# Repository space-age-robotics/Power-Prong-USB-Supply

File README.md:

Power-Prong-USB-Supply
======================

Eagle 6.2 Design files for the Power Prong USB power supply.  It has a selectable 5V or 3v3 volt output (or whatever other MCP1824S voltage regulator that you care to use).  

It has a 250mA polyfuse, with an LED indicator that lights up when the fuse is tripped.

It has connectors for wide breadboards (with 2 power 'lanes' on each side) and narrow (with one power 'lane' per side).

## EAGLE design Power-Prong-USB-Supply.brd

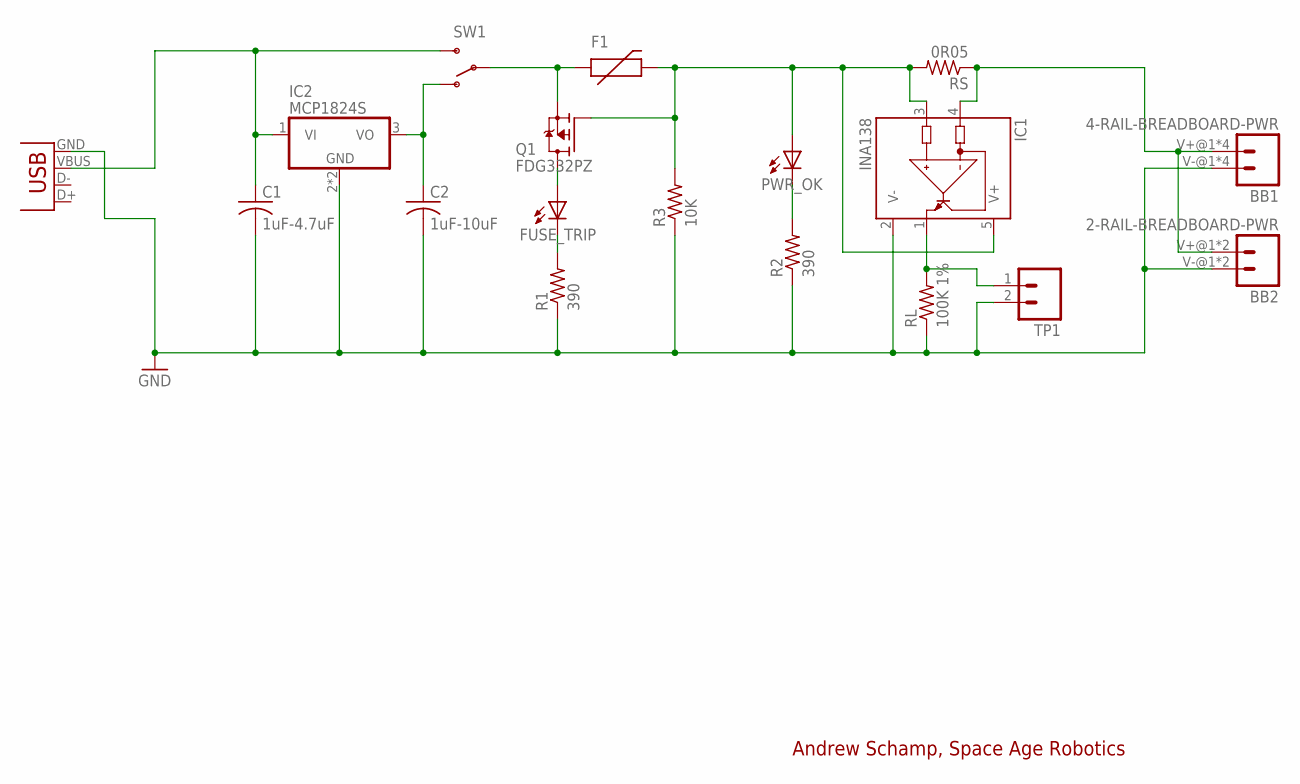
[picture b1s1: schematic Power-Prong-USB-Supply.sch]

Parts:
BB1: 4-RAIL-BREADBOARD-PWR; 4-RAIL-BREADBOARD_X2
BB2: 2-RAIL-BREADBOARD-PWR; 2-RAIL-BREADBOARD
C1: 1uF-4.7uF; C0805
C2: 1uF-10uF; C0805
F1: PTCSMD; PTC-1206
FUSE_TRIP: LEDCHIP-LED0805; CHIP-LED0805
IC1: INA138; SOT23-5
IC2: MCP1824S; SOT223
PWR_OK: LEDCHIP-LED0805; CHIP-LED0805
Q1: FDG332PZ; SC70-6L
R1, R2: 390; R0603
R3: 10K; R0603
RL: 100K 1%; R0805
RS: 0R05; R0805
SW1: SWITCH-SPDTMSH12204; MSH12204
TP1: M023.5MM-NO_SILK; SCREWTERMINAL-3.5MM-2-NS
X1: USBSMD; USB-MINIB

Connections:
GND: BB1.V-@1 (2), BB1.V-@2 (2), BB1.V-@3 (2), BB1.V-@4 (2), BB2.V-@1 (2), BB2.V-@2 (2), C1.2, C2.2, IC1.2 (V-), IC2.2 (GND), IC2.4 (GND), R1.1, R2.1, R3.1, RL.1, TP1.2, X1.GND
unnamed: F1.1, Q1.4 (S), SW1.2
unnamed: C1.1, IC2.1 (VI), SW1.3 (S), X1.VBUS
unnamed: FUSE_TRIP.A, Q1.1 (D), Q1.2 (D), Q1.5 (D), Q1.6 (D)
unnamed: IC1.1 (OUT), RL.2, TP1.1
unnamed: F1.2, IC1.3 (IN+), IC1.5 (V+), PWR_OK.A, Q1.3 (G), R3.2, RS.2
unnamed: PWR_OK.C, R2.2
unnamed: FUSE_TRIP.C, R1.2
unnamed: C2.1, IC2.3 (VO), SW1.1 (O)
VOUT: BB1.V+@1 (1), BB1.V+@2 (1), BB1.V+@3 (1), BB1.V+@4 (1), BB2.V+@1 (1), BB2.V+@2 (1), IC1.4 (IN-), RS.1

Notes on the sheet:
Andrew Schamp, Space Age Robotics

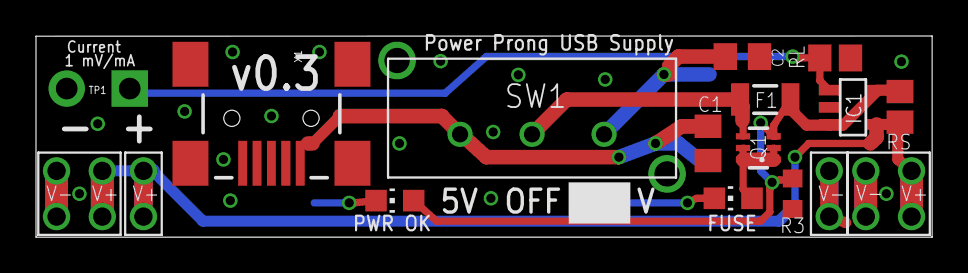
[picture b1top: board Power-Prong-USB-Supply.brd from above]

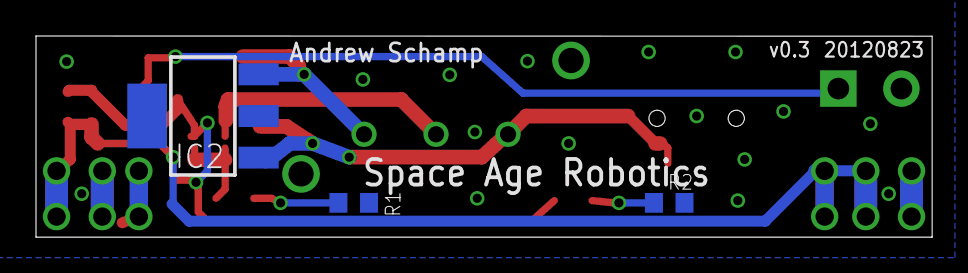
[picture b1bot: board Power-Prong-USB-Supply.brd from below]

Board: 2 copper layers, 49.8 x 11.2 mm, 18 parts (3 on the bottom side), 10 nets.

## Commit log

2012-08-24 v0.3 of Power Prong
2012-08-24 Add images for v0.3
2012-08-24 Fill out readme file
2012-09-07 Resize for panelizing
2012-11-29 Clean up for PCB production

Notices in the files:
Power-Prong-USB-Supply.brd:
CC-BY-SA
parts and their libraries:
SparkFun-PowerIC: Licensing: CC v3.0 Share-Alike You are welcome to use this library for commercial purposes.
space_age_robotics: Released under the Creative Commons
space_age_robotics: http://creativecommons.org/licenses/by-sa/3.0
